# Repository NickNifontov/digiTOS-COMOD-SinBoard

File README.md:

## firmware for UPS Txx 

based on STM32F103C8Tx

half-bridge topology

TrueStudio project

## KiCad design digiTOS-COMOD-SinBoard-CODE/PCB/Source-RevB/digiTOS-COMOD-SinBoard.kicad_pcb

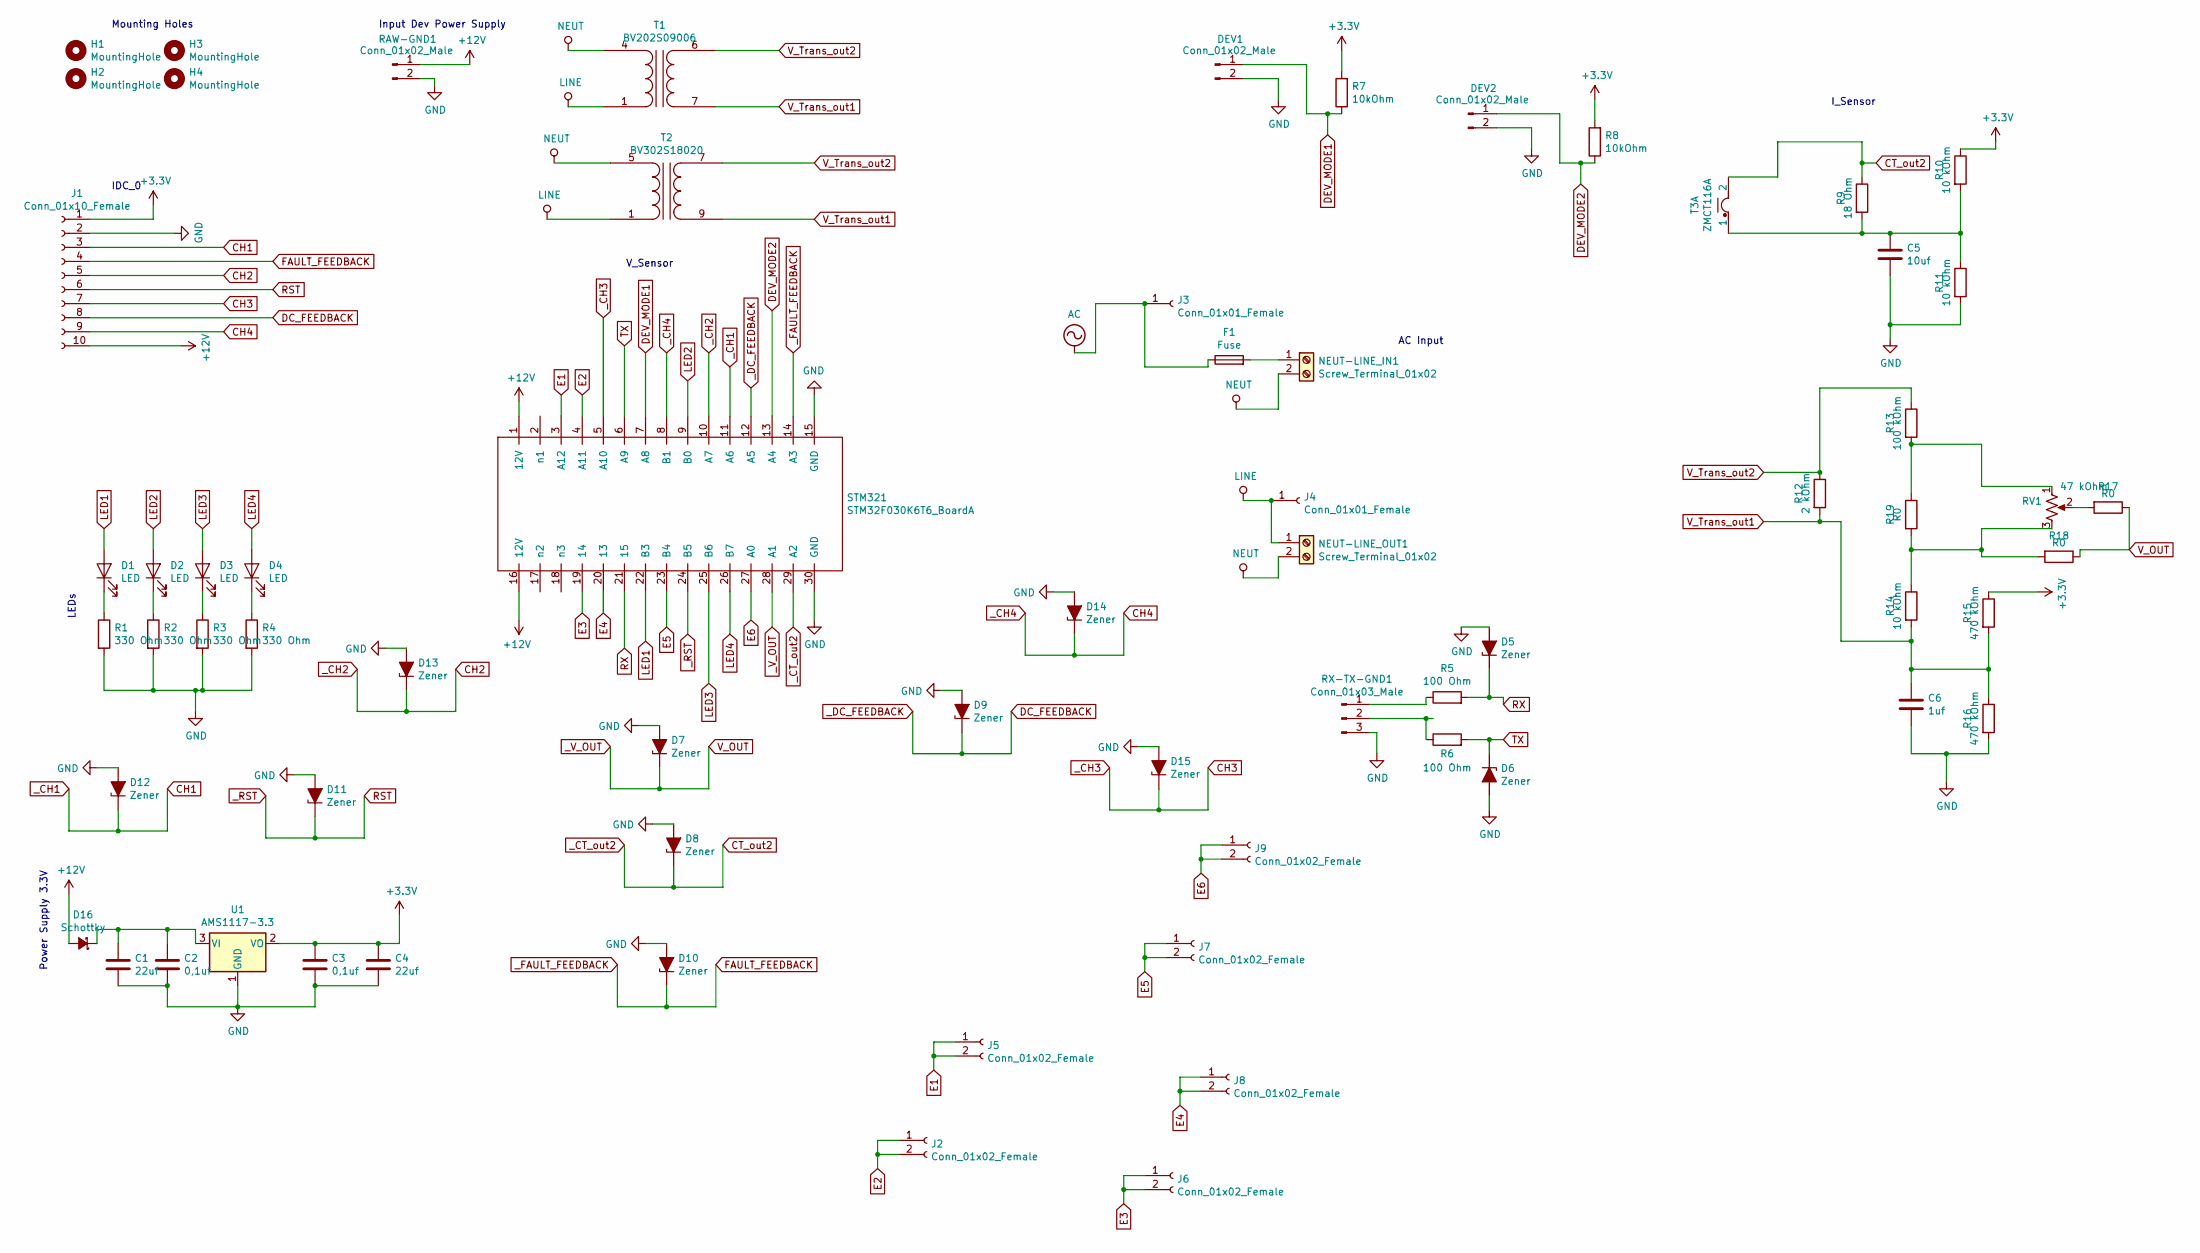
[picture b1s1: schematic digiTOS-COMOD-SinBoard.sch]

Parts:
C1, C4: 22uf; C_1206_3216Metric_Pad1.42x1.75mm_HandSolder
C2, C3: 0,1uf; C_1206_3216Metric_Pad1.42x1.75mm_HandSolder
C5: 10uf; C_1206_3216Metric_Pad1.42x1.75mm_HandSolder
C6: 1uf; C_1206_3216Metric_Pad1.42x1.75mm_HandSolder
D1, D2, D3, D4: LED; LED_1206_3216Metric_Pad1.42x1.75mm_HandSolder
D5, D6, D7, D8, D9, D10, D11, D12, D13, D14, D15: Zener; D_1206_3216Metric_Pad1.42x1.75mm_HandSolder
D16: Schottky; D_SMB
DEV1, DEV2: Conn_01x02_Male; PinSocket_1x02_P2.54mm_Vertical
F1: Fuse; Fuseholder_Blade_Mini_Keystone_3568
H1, H2, H3, H4: MountingHole; MountingHole_4.3mm_M4
J1: Conn_01x10_Female; IDC-Header_2x05_P2.54mm_Vertical
J2, J5, J6, J7, J8, J9: Conn_01x02_Female; PinSocket_1x02_P2.54mm_Vertical
J3, J4: Conn_01x01_Female; SolderWirePad_1x01_Drill2.5mm
NEUT-LINE_IN1: Screw_Terminal_01x02; TerminalBlock_bornier-2_P5.08mm
NEUT-LINE_OUT1: Screw_Terminal_01x02; TerminalBlock_bornier-2_P5.08mm
R1, R2, R3, R4: 330 Ohm; R_1206_3216Metric_Pad1.42x1.75mm_HandSolder
R5, R6: 100 Ohm; R_1206_3216Metric_Pad1.42x1.75mm_HandSolder
R7, R8: 10kOhm; R_1206_3216Metric_Pad1.42x1.75mm_HandSolder
R9: 18 Ohm; R_1206_3216Metric_Pad1.42x1.75mm_HandSolder
R10, R11, R14: 10 kOhm; R_1206_3216Metric_Pad1.42x1.75mm_HandSolder
R12: 2 kOhm; R_1206_3216Metric_Pad1.42x1.75mm_HandSolder
R13: 100 kOhm; R_1206_3216Metric_Pad1.42x1.75mm_HandSolder
R15, R16: 470 kOhm; R_1206_3216Metric_Pad1.42x1.75mm_HandSolder
R17, R18, R19: R0; R_1206_3216Metric_Pad1.42x1.75mm_HandSolder
RAW-GND1: Conn_01x02_Male; PinSocket_1x02_P2.54mm_Vertical
RV1: 47 kOhm; Potentiometer_Bourns_3296W_Vertical
RX-TX-GND1: Conn_01x03_Male; PinSocket_1x03_P2.54mm_Vertical
STM321: STM32F030K6T6_BoardA
T1: BV202S09006
T2: BV302S18020
T3: ZMCT116A
U1: AMS1117-3.3; SOT-223-3_TabPin2

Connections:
+3V3: C3.1, C4.1, J1.1, R7.2, R8.2, R10.1, R15.1, U1.2 (VO)
+12V: D16.2 (A), J1.10, RAW-GND1.1, STM321.1 (12V), STM321.16 (12V)
AC: F1.1, J3.1
CH1: D12.1 (K), J1.3, STM321.11 (A6)
CH2: D13.1 (K), J1.5, STM321.10 (A7)
CH3: D15.1 (K), J1.7, STM321.5 (A10)
CH4: D14.1 (K), J1.9, STM321.8 (B1)
CT_out2: D8.1 (K), R9.1, STM321.29 (A2), T3.2
DC_FEEDBACK: D9.1 (K), J1.8, STM321.12 (A5)
DEV_MODE1: DEV1.1, R7.1, STM321.7 (A8)
DEV_MODE2: DEV2.1, R8.1, STM321.13 (A4)
E1: J5.1, J5.2, STM321.3 (A12)
E2: J2.1, J2.2, STM321.4 (A11)
E3: J6.1, J6.2, STM321.19 (14)
E4: J8.1, J8.2, STM321.20 (13)
E5: J7.1, J7.2, STM321.23 (B4)
E6: J9.1, J9.2, STM321.27 (A0)
FAULT_FEEDBACK: D10.1 (K), J1.4, STM321.14 (A3)
GND: C1.2, C2.2, C3.2, C4.2, C5.2, C6.2, D5.2 (A), D6.2 (A), D7.2 (A), D8.2 (A), D9.2 (A), D10.2 (A), D11.2 (A), D12.2 (A), D13.2 (A), D14.2 (A), D15.2 (A), DEV1.2, DEV2.2, J1.2, R1.2, R2.2, R3.2, R4.2, R11.2, R16.2, RAW-GND1.2, RX-TX-GND1.3, STM321.15 (GND), STM321.30 (GND), U1.1 (GND)
LED1: D1.2 (A), STM321.22 (B3)
LED2: D2.2 (A), STM321.9 (B0)
LED3: D3.2 (A), STM321.25 (B6)
LED4: D4.2 (A), STM321.26 (B7)
LINE: J4.1, NEUT-LINE_OUT1.1, T1.1 (AB), T2.1 (AB)
NEUT: NEUT-LINE_IN1.2, NEUT-LINE_OUT1.2, T1.4 (AA), T2.5 (AA)
unnamed: C1.1, C2.1, D16.1 (K), U1.3 (VI)
unnamed: C5.1, R9.2, R10.2, R11.1, T3.1
unnamed: D1.1 (K), R1.1
unnamed: D2.1 (K), R2.1
unnamed: D3.1 (K), R3.1
unnamed: D4.1 (K), R4.1
unnamed: F1.2, NEUT-LINE_IN1.1
unnamed: R5.1, RX-TX-GND1.1
unnamed: R6.1, RX-TX-GND1.2
unnamed: R13.2, R19.1, RV1.1
unnamed: R14.1, R18.2, R19.2, RV1.3
unnamed: R17.2, RV1.2
unnamed: T3.3, T3.4, T3.5
RST: D11.1 (K), J1.6, STM321.24 (B5)
RX: D5.1 (K), R5.2, STM321.21 (15)
TX: D6.1 (K), R6.2, STM321.6 (A9)
V_OUT: D7.1 (K), R17.1, R18.1, STM321.28 (A1)
V_Trans_out1: C6.1, R12.2, R14.2, R15.2, R16.1, T1.7 (SA), T2.9 (SA)
V_Trans_out2: R12.1, R13.1, T1.6 (SB), T2.7 (SB)

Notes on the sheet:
Mounting Holes
Input Dev Power Supply
IDC_0
V_Sensor
I_Sensor
AC Input
LEDs
Power Supply 3.3V

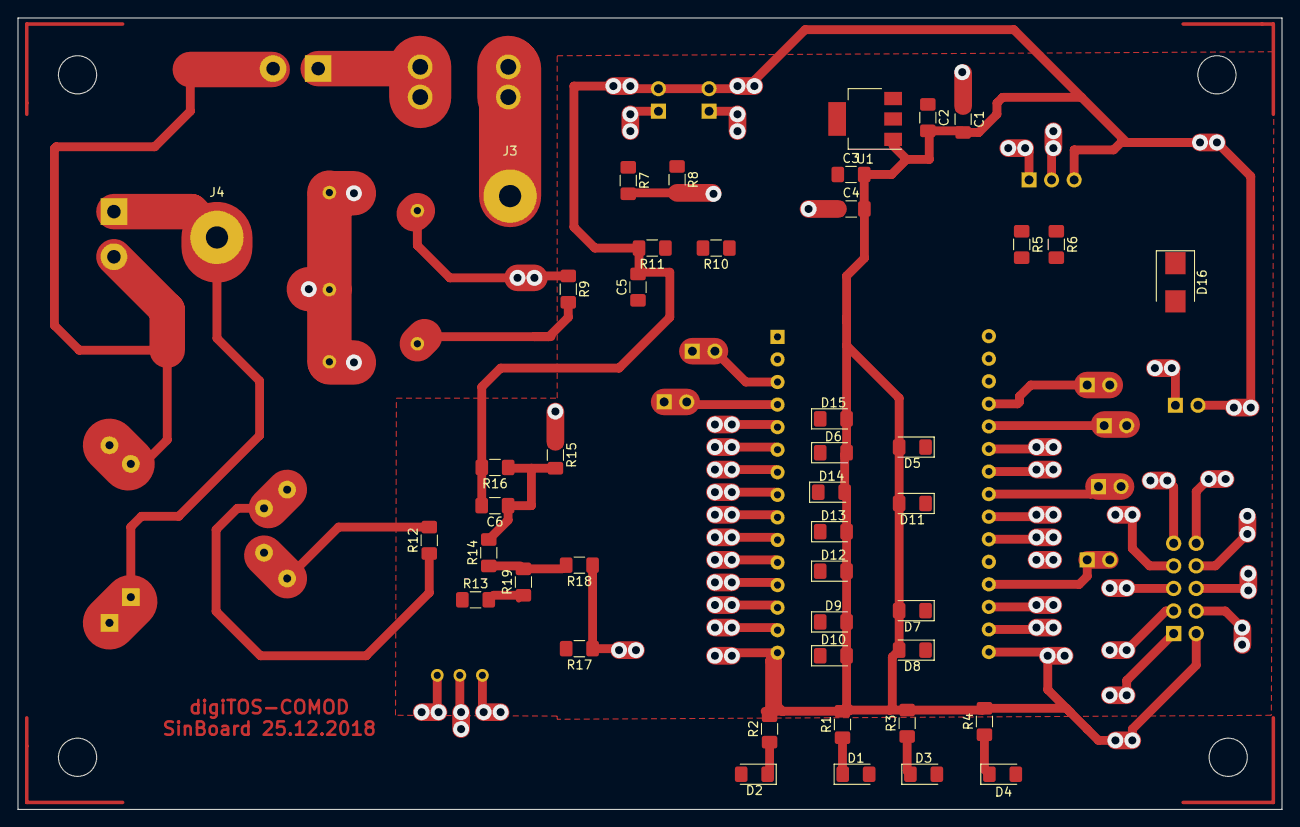
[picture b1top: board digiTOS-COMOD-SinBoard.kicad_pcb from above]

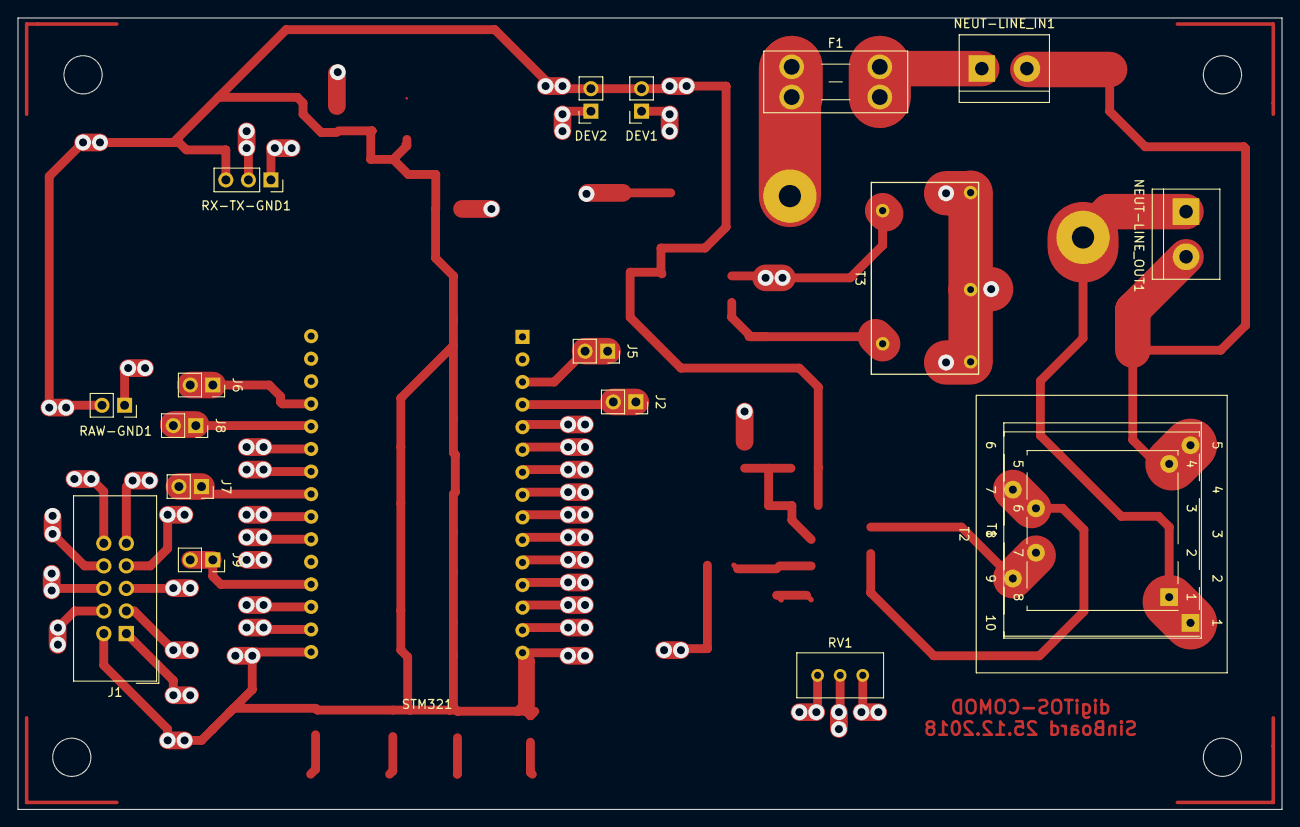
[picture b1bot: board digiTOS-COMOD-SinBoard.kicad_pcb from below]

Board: 2 copper layers, 142.3 x 89.1 mm, 67 parts (19 on the bottom side), 44 nets.

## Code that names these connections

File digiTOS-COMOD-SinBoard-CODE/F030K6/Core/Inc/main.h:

/* USER CODE BEGIN Header */
/**
  ******************************************************************************
  * @file           : main.h
  * @brief          : Header for main.c file.
  *                   This file contains the common defines of the application.
  ******************************************************************************
  ** This notice applies to any and all portions of this file
  * that are not between comment pairs USER CODE BEGIN and
  * USER CODE END. Other portions of this file, whether 
  * inserted by the user or by software development tools
  * are owned by their respective copyright owners.
  *
  * COPYRIGHT(c) 2018 STMicroelectronics
  *
  * Redistribution and use in source and binary forms, with or without modification,
  * are permitted provided that the following conditions are met:
  *   1. Redistributions of source code must retain the above copyright notice,
  *      this list of conditions and the following disclaimer.
  *   2. Redistributions in binary form must reproduce the above copyright notice,
  *      this list of conditions and the following disclaimer in the documentation
  *      and/or other materials provided with the distribution.
  *   3. Neither the name of STMicroelectronics nor the names of its contributors
  *      may be used to endorse or promote products derived from this software
  *      without specific prior written permission.
  *
  * THIS SOFTWARE IS PROVIDED BY THE COPYRIGHT HOLDERS AND CONTRIBUTORS "AS IS"
  * AND ANY EXPRESS OR IMPLIED WARRANTIES, INCLUDING, BUT NOT LIMITED TO, THE
  * IMPLIED WARRANTIES OF MERCHANTABILITY AND FITNESS FOR A PARTICULAR PURPOSE ARE
  * DISCLAIMED. IN NO EVENT SHALL THE COPYRIGHT HOLDER OR CONTRIBUTORS BE LIABLE
  * FOR ANY DIRECT, INDIRECT, INCIDENTAL, SPECIAL, EXEMPLARY, OR CONSEQUENTIAL
  * DAMAGES (INCLUDING, BUT NOT LIMITED TO, PROCUREMENT OF SUBSTITUTE GOODS OR
  * SERVICES; LOSS OF USE, DATA, OR PROFITS; OR BUSINESS INTERRUPTION) HOWEVER
  * CAUSED AND ON ANY THEORY OF LIABILITY, WHETHER IN CONTRACT, STRICT LIABILITY,
  * OR TORT (INCLUDING NEGLIGENCE OR OTHERWISE) ARISING IN ANY WAY OUT OF THE USE
  * OF THIS SOFTWARE, EVEN IF ADVISED OF THE POSSIBILITY OF SUCH DAMAGE.
  *
  ******************************************************************************
  */
/* USER CODE END Header */

/* Define to prevent recursive inclusion -------------------------------------*/
#ifndef __MAIN_H
#define __MAIN_H

#ifdef __cplusplus
extern "C" {
#endif

/* Includes ------------------------------------------------------------------*/
#include "stm32f0xx_hal.h"

/* Private includes ----------------------------------------------------------*/
/* USER CODE BEGIN Includes */

/* USER CODE END Includes */

/* Exported types ------------------------------------------------------------*/
/* USER CODE BEGIN ET */

/* USER CODE END ET */

/* Exported constants --------------------------------------------------------*/
/* USER CODE BEGIN EC */

/* USER CODE END EC */

/* Exported macro ------------------------------------------------------------*/
/* USER CODE BEGIN EM */

/* USER CODE END EM */

/* Exported functions prototypes ---------------------------------------------*/
void Error_Handler(void);

/* USER CODE BEGIN EFP */

/* USER CODE END EFP */

/* Private defines -----------------------------------------------------------*/
#define PF0_Pin GPIO_PIN_0
#define PF0_GPIO_Port GPIOF
#define PF1_Pin GPIO_PIN_1
#define PF1_GPIO_Port GPIOF
#define V_OUT_Pin GPIO_PIN_1
#define V_OUT_GPIO_Port GPIOA
#define C_OUT_Pin GPIO_PIN_2
#define C_OUT_GPIO_Port GPIOA
#define FAULT_FEEDBACK_Pin GPIO_PIN_3
#define FAULT_FEEDBACK_GPIO_Port GPIOA
#define DEV_MODE2_Pin GPIO_PIN_4
#define DEV_MODE2_GPIO_Port GPIOA
#define DC_FEEDBACK_Pin GPIO_PIN_5
#define DC_FEEDBACK_GPIO_Port GPIOA
#define CH1_Pin GPIO_PIN_6
#define CH1_GPIO_Port GPIOA
#define CH2_Pin GPIO_PIN_7
#define CH2_GPIO_Port GPIOA
#define LED2_Pin GPIO_PIN_0
#define LED2_GPIO_Port GPIOB
#define CH4_Pin GPIO_PIN_1
#define CH4_GPIO_Port GPIOB
#define DEV_MODE1_Pin GPIO_PIN_8
#define DEV_MODE1_GPIO_Port GPIOA
#define TX_Pin GPIO_PIN_9
#define TX_GPIO_Port GPIOA
#define CH3_Pin GPIO_PIN_10
#define CH3_GPIO_Port GPIOA
#define RX_Pin GPIO_PIN_15
#define RX_GPIO_Port GPIOA
#define LED1_Pin GPIO_PIN_3
#define LED1_GPIO_Port GPIOB
#define RST_Pin GPIO_PIN_5
#define RST_GPIO_Port GPIOB
#define LED3_Pin GPIO_PIN_6
#define LED3_GPIO_Port GPIOB
#define LED4_Pin GPIO_PIN_7
#define LED4_GPIO_Port GPIOB
#define CALIBV_Pin GPIO_PIN_11
#define CALIBV_GPIO_Port GPIOA
#define CALIBI_Pin GPIO_PIN_12
#define CALIBI_GPIO_Port GPIOA
#define CALIBMODE_Pin GPIO_PIN_0
#define CALIBMODE_GPIO_Port GPIOA
/* USER CODE BEGIN Private defines */

/* USER CODE END Private defines */

#ifdef __cplusplus
}
#endif

#endif /* __MAIN_H */

/************************ (C) COPYRIGHT STMicroelectronics *****END OF FILE****/

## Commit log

2019-01-02 Second commit
2019-01-02 On ADC
2019-01-02 Set theme jekyll-theme-minimal
2019-01-02 Prepare release
2019-01-02 prepare
2019-01-02 disable ADC DMA
2019-01-02 enable ADC DMA
2019-01-02 removed trash
2019-01-02 added PCB files
2019-01-02 added PCB
2019-01-02 update after PCB
2019-01-02 ready to RevA
2019-01-02 update RevA
2019-01-02 Update issue templates
2019-01-02 updated Stm32CubeMx porject
2019-01-02 added two type of V_out - linear form and sinus form
2019-01-02 Rev B
2019-01-03 SetInverseSignal -> SetNormalSignal
2019-01-03 updated MinSinusData->30 updated MaxSinusData->970
2019-01-03 updated Sinus table with 60% height, updated Amp coef 0.4-1.6 range now, added autocalculation of Amp_step
2019-01-03 check FaultFlag at boot mode (first Start)
2019-01-04 pre-ready
2019-01-04 ready
2019-01-04 fixed bug with Amplituda correction, thanks to mkonder
2019-01-04 fixed amplitude bugs, Mkonder commit update
2019-01-05 fixed bugs with V_out, added Global Configuration file, added Softstart
2019-01-05 global update
2019-01-05 added AMP_PROTECTION
2019-01-05 added DC_FEEDBACK protection
2019-01-06 added code to Debug variables thanks to MKonder, added DC_PROTECTION Roll-Back level
2019-01-06 update settings
2019-01-06 fixed bug in stm32f0xx_hal_crc.c
2019-01-06 removed unused files
2019-01-06 fixed small bugs
2019-01-06 updates global
2019-01-06 pre-release
2019-01-06 pre-release RevB+
2019-01-06 release
2019-01-07 RELEASE !
2019-01-07 updated Render Pin-Map
2019-01-07 added STM32F103C8Tx template
2019-01-08 remuve la la
2019-01-08 # WARNING: head commit changed in the meantime
    lala
2019-01-08 add gitignore *.o *.su
2019-01-10 Chenge interrupt priority, sihronize tim1&tim3 PWM
2019-01-10 test
2019-01-12 uodate
2019-01-13 backup
2019-01-13 update CubeMX project
2019-01-14 updata 20190114
2019-01-15 repare 50hz sinhro
2019-01-15 refresh
2019-01-15 reset to 50hz sinhro
2019-01-15 small updates
2019-01-16 Refacor HAL_TIM_MspPostInit on TIM1
2019-01-17 ref 1
